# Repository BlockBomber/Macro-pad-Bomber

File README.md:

List of all the parts:
1) Seeed XIAO RP2040
2) MX-Style switches (x16)
3) 0.91 inch OLED displays
4) Blank DSA keycaps (x16)
5) SK6812 MINI-E LEDs (x16)
6) M3x16mm (x4)
7) Through-hole 1N4148 Diodes (x4)

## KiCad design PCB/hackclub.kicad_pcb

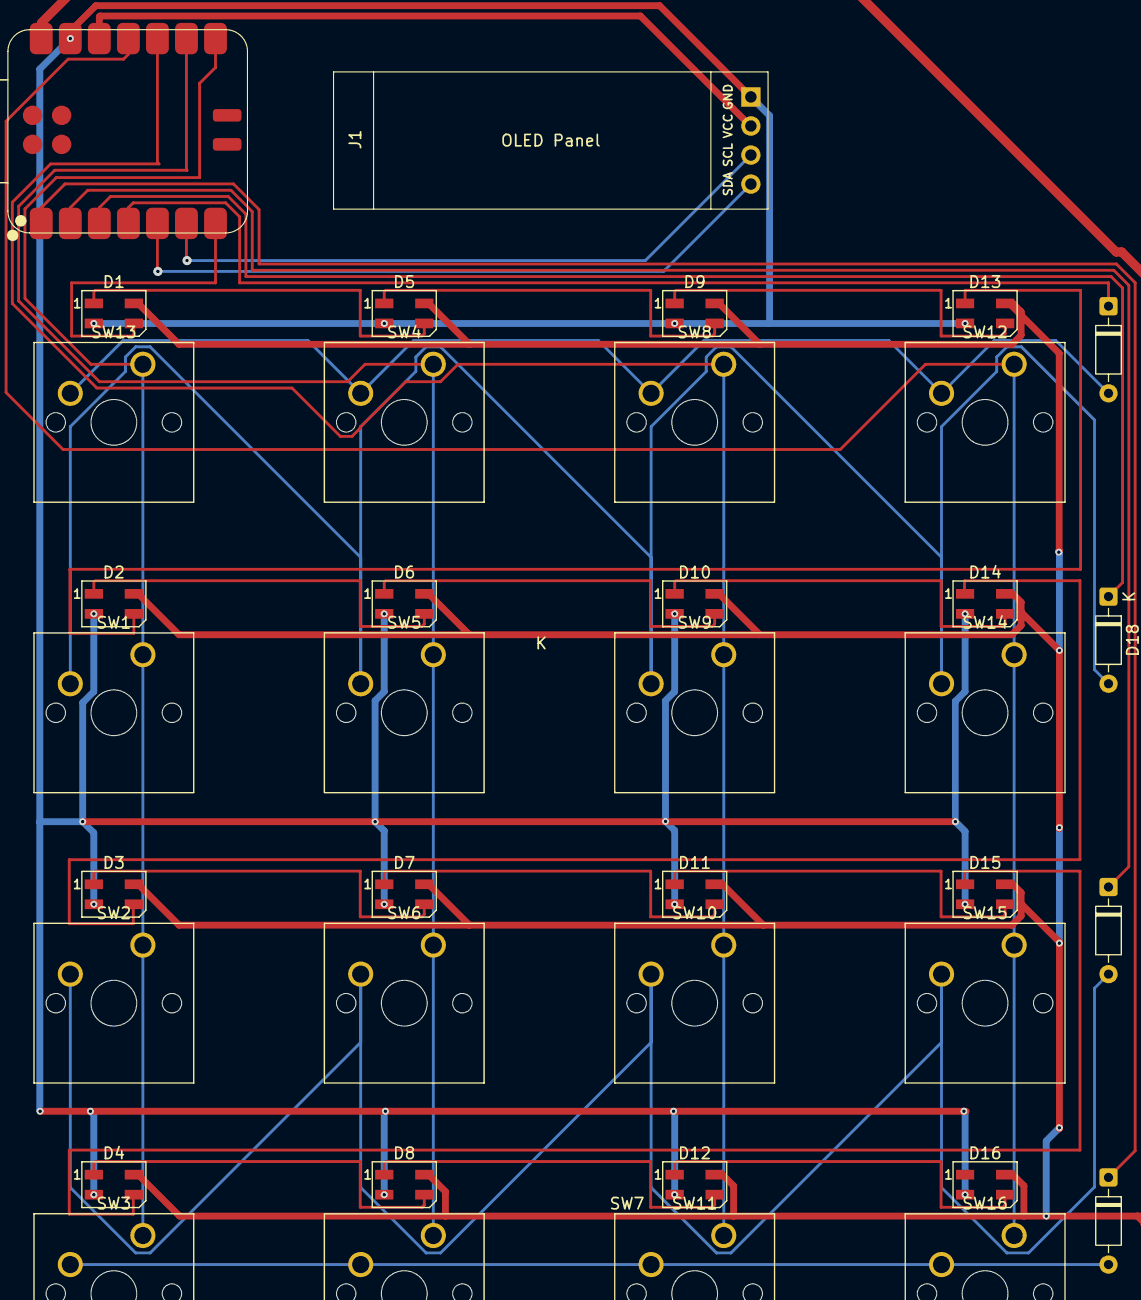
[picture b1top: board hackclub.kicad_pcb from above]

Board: 2 copper layers, 38 parts (0 on the bottom side), 33 nets.

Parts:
D1, D2, D3, D4, D5, D6, D7, D8, D9, D10, D11, D12, D13, D14, D15, D16: SK6812MINI; LED_SK6812MINI_PLCC4_3.5x3.5mm_P1.75mm
D17, D18, D19, D20: 1N4148; D_DO-35_SOD27_P7.62mm_Horizontal
J1: OLED; SSD1306-0.91-OLED-4pin-128x32
SW1, SW2, SW3, SW4, SW5, SW6, SW7, SW8, SW9, SW10, SW11, SW12, SW13, SW14, SW15, SW16: SW_Push; SW_Cherry_MX_1.00u_PCB
U1: XIAO-RP2040-DIP; XIAO-RP2040-SMD

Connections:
+3V3: J1.2, U1.12 (3V3)
+5V: D1.4 (VDD), D2.4 (VDD), D3.4 (VDD), D4.4 (VDD), D5.4 (VDD), D6.4 (VDD), D7.4 (VDD), D8.4 (VDD), D9.4 (VDD), D10.4 (VDD), D11.4 (VDD), D12.4 (VDD), D13.4 (VDD), D14.4 (VDD), D15.4 (VDD), D16.4 (VDD), U1.14 (VBUS)
GND: D1.2 (VSS), D2.2 (VSS), D3.2 (VSS), D4.2 (VSS), D5.2 (VSS), D6.2 (VSS), D7.2 (VSS), D8.2 (VSS), D9.2 (VSS), D10.2 (VSS), D11.2 (VSS), D12.2 (VSS), D13.2 (VSS), D14.2 (VSS), D15.2 (VSS), D16.2 (VSS), J1.1, U1.13 (GND)
unnamed: D1.3 (DIN), U1.7 (GPIO0/TX)
unnamed: D1.1 (DOUT), D5.3 (DIN)
unnamed: D2.1 (DOUT), D6.3 (DIN)
unnamed: D3.1 (DOUT), D7.3 (DIN)
unnamed: D4.1 (DOUT), D8.3 (DIN)
unnamed: D5.1 (DOUT), D9.3 (DIN)
unnamed: D6.1 (DOUT), D10.3 (DIN)
unnamed: D10.1 (DOUT), D14.3 (DIN)
unnamed: D7.1 (DOUT), D11.3 (DIN)
unnamed: D11.1 (DOUT), D15.3 (DIN)
unnamed: D8.1 (DOUT), D12.3 (DIN)
unnamed: D12.1 (DOUT), D16.3 (DIN)
unnamed: D9.1 (DOUT), D13.3 (DIN)
unnamed: D2.3 (DIN), D13.1 (DOUT)
unnamed: D3.3 (DIN), D14.1 (DOUT)
unnamed: D4.3 (DIN), D15.1 (DOUT)
unnamed: D17.2 (A), SW4.2, SW8.2, SW12.2, SW13.2
unnamed: D17.1 (K), U1.4 (GPIO29/ADC3/A3)
unnamed: D18.2 (A), SW1.2, SW5.2, SW9.2, SW14.2
unnamed: D18.1 (K), U1.3 (GPIO28/ADC2/A2)
unnamed: D19.2 (A), SW2.2, SW6.2, SW10.2, SW15.2
unnamed: D19.1 (K), U1.2 (GPIO27/ADC1/A1)
unnamed: D20.2 (A), SW3.2, SW7.2, SW11.2, SW16.2
unnamed: D20.1 (K), U1.1 (GPIO26/ADC0/A0)
unnamed: J1.4, U1.5 (GPIO6/SDA)
unnamed: J1.3, U1.6 (GPIO7/SCL)
unnamed: SW1.1, SW2.1, SW3.1, SW13.1, U1.8 (GPIO1/RX)
unnamed: SW4.1, SW5.1, SW6.1, SW7.1, U1.9 (GPIO2/SCK)
unnamed: SW12.1, SW14.1, SW15.1, SW16.1, U1.11 (GPIO3/MOSI)
unnamed: SW8.1, SW9.1, SW10.1, SW11.1, U1.10 (GPIO4/MISO)

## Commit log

2025-12-06 README.md
    List of parts
